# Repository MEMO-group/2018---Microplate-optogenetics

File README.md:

# Microplate illuminator

CAD model and 3D-printed prototype of the microplate illuminator. The assembled circuit board is affixed to the printed housing using mouldable glue or screws,and programmed via the serial interface header and the Arduino software.  During operation a microplate is placed on top of the device, which is then incubated on a microplate shaker; the microplate should have opaque wals and a transparant lid, the incubator should be placed in a darkened room without reflective surfaces or covered with e.g. a styrofoam cooler lined with black felt.

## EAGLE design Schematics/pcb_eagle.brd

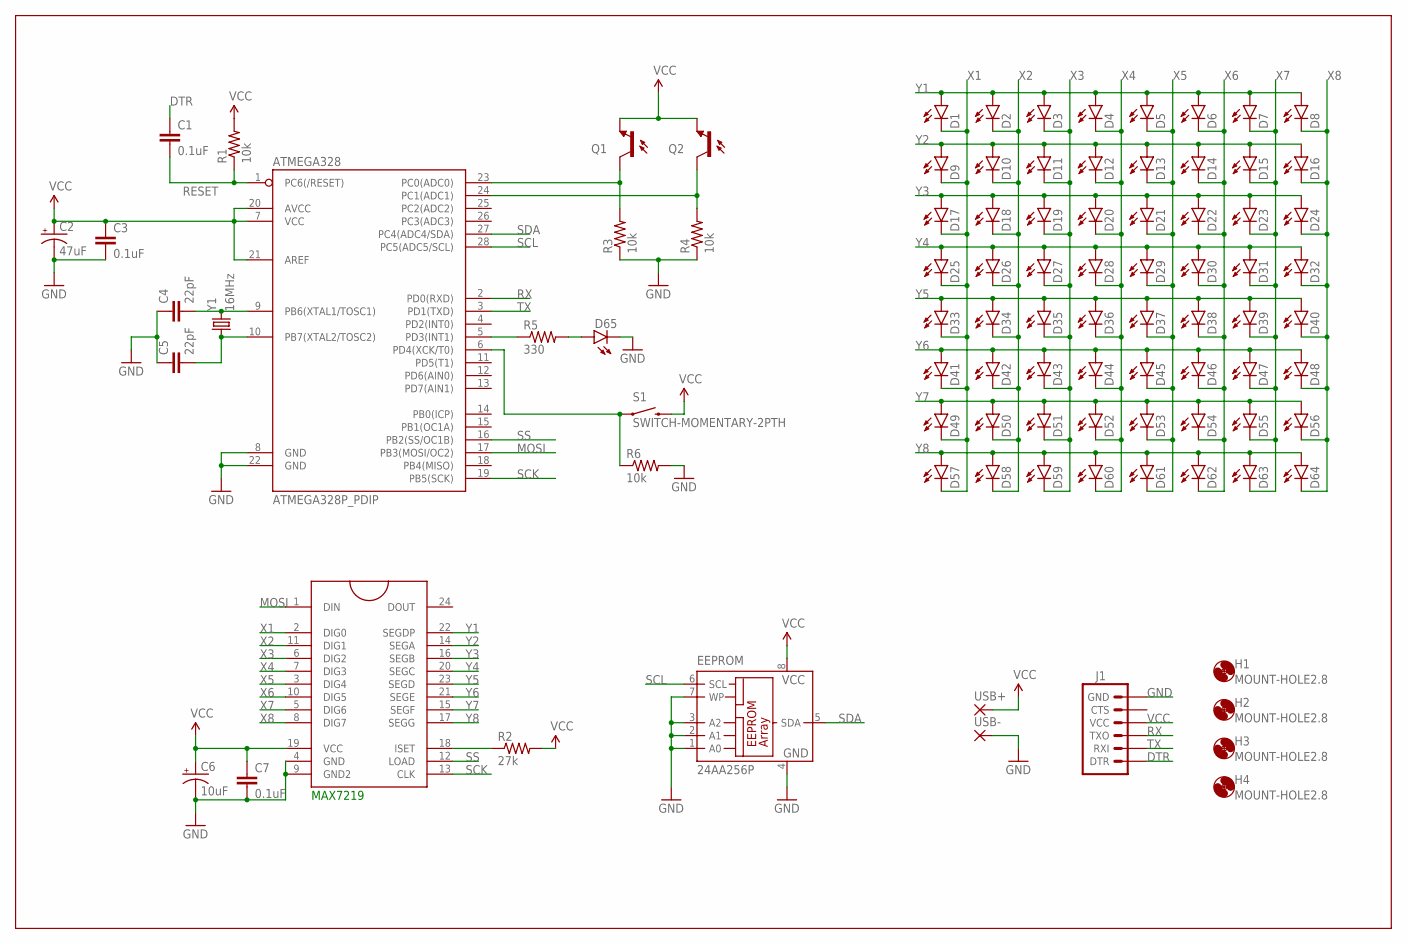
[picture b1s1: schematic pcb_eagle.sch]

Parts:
ATMEGA328: ATMEGA328P_PDIP; DIL28-3
C1, C3, C7: 0.1uF; CAP-PTH-SMALL
C2: 47uF; CPOL-RADIAL-10UF-25V
C4, C5: 22pF; CAP-PTH-SMALL
C6: 10uF; CPOL-RADIAL-10UF-25V
D1, D2, D3, D4, D5, D6, D7, D8, D9, D10, D11, D12, D13, D14, D15, D16, D17, D18, D19, D20, D21, D22, D23, D24, D25, D26, D27, D28, D29, D30, D31, D32, D33, D34, D35, D36, D37, D38, D39, D40, D41, D42, D43, D44, D45, D46, D47, D48, D49, D50, D51, D52, D53, D54, D55, D56, D57, D58, D59, D60, D61, D62, D63, D64, D65: LED3MM
EEPROM: 24AA256P; DIL8
H1, H2, H3, H4: MOUNT-HOLE2.8; 2,8
J1: ARDUINO_SERIAL_PROGRAMPTH; 1X06
MAX72191: MAX7219DIP; DIL24
Q1, Q2: PHOTOTRANSISTORT1; LED3MM
R1, R3, R4, R6: 10k; AXIAL-0.3
R2: 27k; AXIAL-0.3
R5: 330; AXIAL-0.3
S1: SWITCH-MOMENTARY-2PTH; TACTILE-PTH
USB+: 2,54/0,9
USB-: 2,54/0,9
Y1: 16MHz; HC49US

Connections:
DTR: C1.1, J1.1 (DTR)
GND: ATMEGA328.8 (GND), ATMEGA328.22 (GND), C2.2 (-), C3.2, C4.1, C5.1, C6.2 (-), C7.2, D65.K (C), EEPROM.1 (A0), EEPROM.2 (A1), EEPROM.3 (A2), EEPROM.4 (GND), EEPROM.7 (WP), J1.6 (GND), MAX72191.4 (GND), MAX72191.9 (GND2), R3.P$1 (1), R4.P$1 (1), R6.P$2 (2), USB-.1
MOSI: ATMEGA328.17 (PB3(MOSI/OC2)), MAX72191.1 (DIN)
unnamed: ATMEGA328.9 (PB6(XTAL1/TOSC1)), C4.2, Y1.2
unnamed: ATMEGA328.10 (PB7(XTAL2/TOSC2)), C5.2, Y1.1
unnamed: MAX72191.18 (ISET), R2.P$1 (1)
unnamed: ATMEGA328.24 (PC1(ADC1)), Q2.C, R4.P$2 (2)
unnamed: ATMEGA328.23 (PC0(ADC0)), Q1.C, R3.P$2 (2)
unnamed: ATMEGA328.5 (PD3(INT1)), R5.P$1 (1)
unnamed: D65.A, R5.P$2 (2)
unnamed: ATMEGA328.6 (PD4(XCK/T0)), R6.P$1 (1), S1.1
RESET: ATMEGA328.1 (PC6(/RESET)), C1.2, R1.P$1 (1)
RX: ATMEGA328.2 (PD0(RXD)), J1.3 (TXO)
SCK: ATMEGA328.19 (PB5(SCK)), MAX72191.13 (CLK)
SCL: ATMEGA328.28 (PC5(ADC5/SCL)), EEPROM.6 (SCL)
SDA: ATMEGA328.27 (PC4(ADC4/SDA)), EEPROM.5 (SDA)
SS: ATMEGA328.16 (PB2(SS/OC1B)), MAX72191.12 (LOAD)
TX: ATMEGA328.3 (PD1(TXD)), J1.2 (RXI)
VCC: ATMEGA328.7 (VCC), ATMEGA328.20 (AVCC), ATMEGA328.21 (AREF), C2.1 (+), C3.1, C6.1 (+), C7.1, EEPROM.8 (VCC), J1.4 (VCC), MAX72191.19 (VCC), Q1.E, Q2.E, R1.P$2 (2), R2.P$2 (2), S1.3 (2), USB+.1
X1: D1.K (C), D9.K (C), D17.K (C), D25.K (C), D33.K (C), D41.K (C), D49.K (C), D57.K (C), MAX72191.2 (DIG0)
X2: D2.K (C), D10.K (C), D18.K (C), D26.K (C), D34.K (C), D42.K (C), D50.K (C), D58.K (C), MAX72191.11 (DIG1)
X3: D3.K (C), D11.K (C), D19.K (C), D27.K (C), D35.K (C), D43.K (C), D51.K (C), D59.K (C), MAX72191.6 (DIG2)
X4: D4.K (C), D12.K (C), D20.K (C), D28.K (C), D36.K (C), D44.K (C), D52.K (C), D60.K (C), MAX72191.7 (DIG3)
X5: D5.K (C), D13.K (C), D21.K (C), D29.K (C), D37.K (C), D45.K (C), D53.K (C), D61.K (C), MAX72191.3 (DIG4)
X6: D6.K (C), D14.K (C), D22.K (C), D30.K (C), D38.K (C), D46.K (C), D54.K (C), D62.K (C), MAX72191.10 (DIG5)
X7: D7.K (C), D15.K (C), D23.K (C), D31.K (C), D39.K (C), D47.K (C), D55.K (C), D63.K (C), MAX72191.5 (DIG6)
X8: D8.K (C), D16.K (C), D24.K (C), D32.K (C), D40.K (C), D48.K (C), D56.K (C), D64.K (C), MAX72191.8 (DIG7)
Y1: D1.A, D2.A, D3.A, D4.A, D5.A, D6.A, D7.A, D8.A, MAX72191.22 (SEGDP)
Y2: D9.A, D10.A, D11.A, D12.A, D13.A, D14.A, D15.A, D16.A, MAX72191.14 (SEGA)
Y3: D17.A, D18.A, D19.A, D20.A, D21.A, D22.A, D23.A, D24.A, MAX72191.16 (SEGB)
Y4: D25.A, D26.A, D27.A, D28.A, D29.A, D30.A, D31.A, D32.A, MAX72191.20 (SEGC)
Y5: D33.A, D34.A, D35.A, D36.A, D37.A, D38.A, D39.A, D40.A, MAX72191.23 (SEGD)
Y6: D41.A, D42.A, D43.A, D44.A, D45.A, D46.A, D47.A, D48.A, MAX72191.21 (SEGE)
Y7: D49.A, D50.A, D51.A, D52.A, D53.A, D54.A, D55.A, D56.A, MAX72191.15 (SEGF)
Y8: D57.A, D58.A, D59.A, D60.A, D61.A, D62.A, D63.A, D64.A, MAX72191.17 (SEGG)

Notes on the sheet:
MAX7219

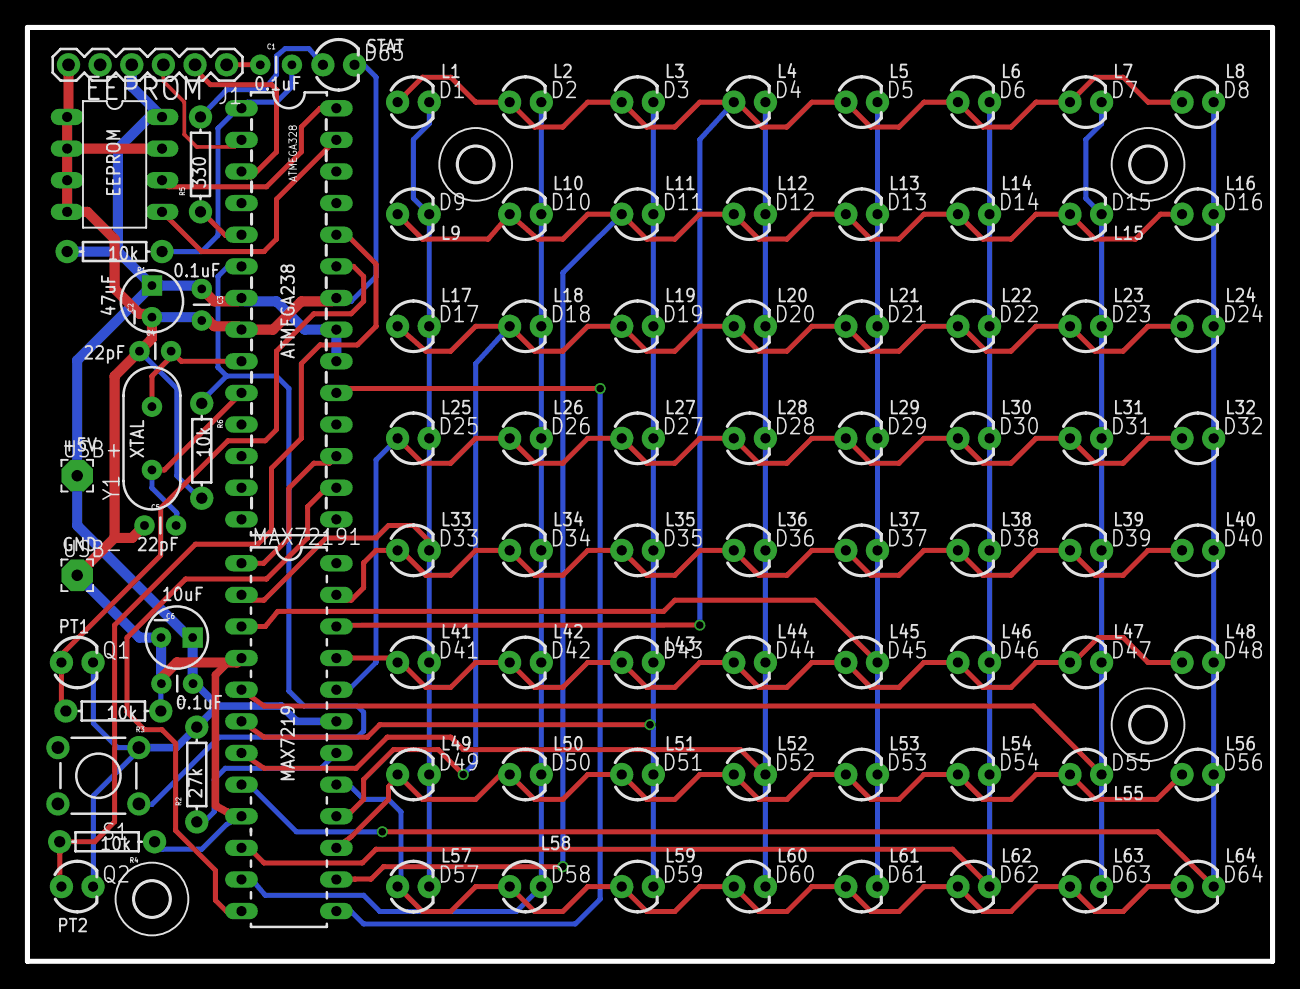
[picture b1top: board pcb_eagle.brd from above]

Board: 2 copper layers, 100.0 x 75.0 mm, 92 parts (0 on the bottom side), 35 nets.

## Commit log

2018-09-24 Added plasmid files.

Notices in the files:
parts and their libraries:
SparkFun-Capacitors: Licensing: Creative Commons ShareAlike 4.0 International - https://creativecommons.org/licenses/by-sa/4.0
